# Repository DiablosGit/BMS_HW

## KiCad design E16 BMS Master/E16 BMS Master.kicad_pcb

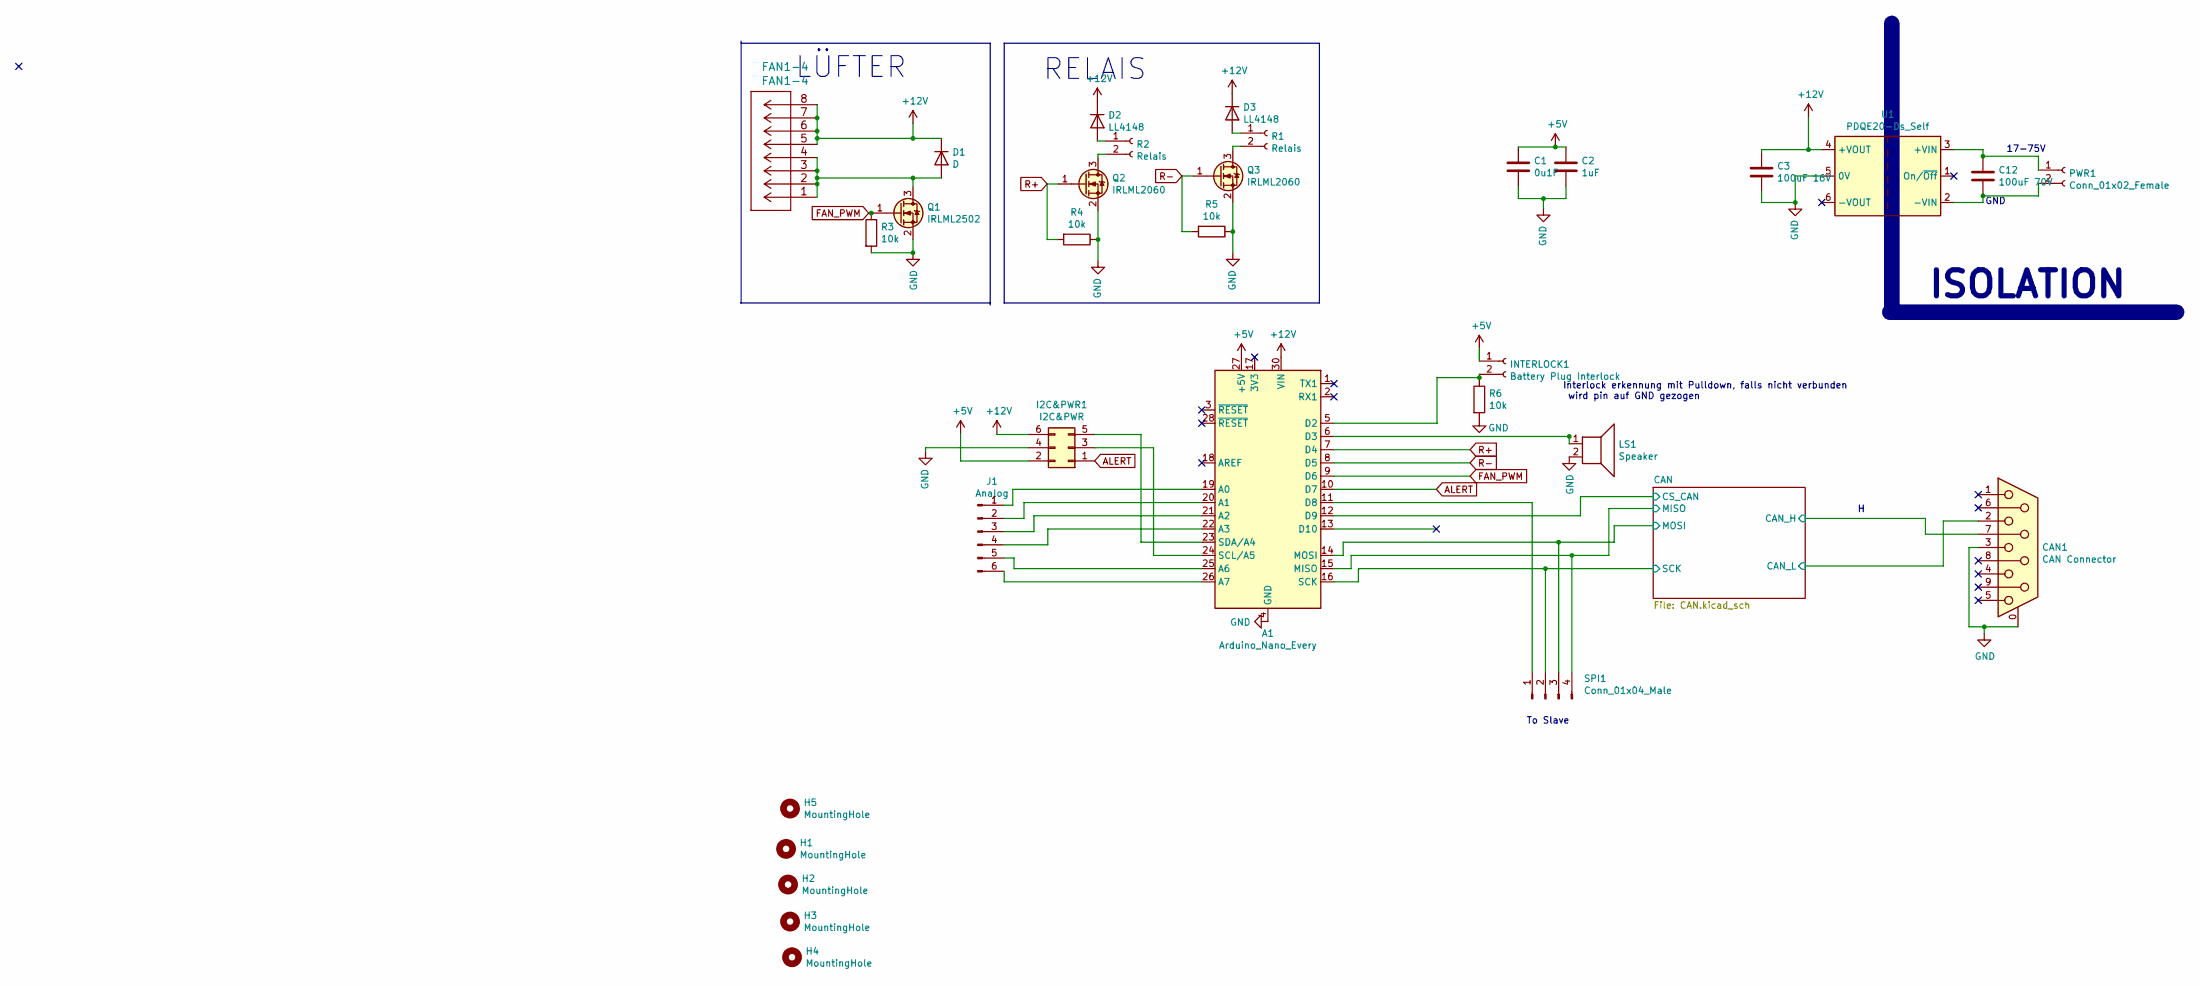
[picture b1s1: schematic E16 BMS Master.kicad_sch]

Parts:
A1: Arduino_Nano_Every; Arduino_Nano
C1: 0u1F; C_1206_3216Metric_Pad1.33x1.80mm_HandSolder
C2: 1uF; C_1206_3216Metric_Pad1.33x1.80mm_HandSolder
C3: 100uF 16V; C_1206_3216Metric_Pad1.33x1.80mm_HandSolder
C12: 100uF 70V; C_1206_3216Metric_Pad1.33x1.80mm_HandSolder
CAN1: CAN Connector; DSUB-9_Female_Horizontal_P2.77x2.84mm_EdgePinOffset7.70mm_H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
D1: D; D_MiniMELF
D2, D3: LL4148; D_MiniMELF
FAN1-4: FAN1-4; 449145803
H1, H2, H3, H4: MountingHole; MountingHole_3.2mm_M3_ISO7380
H5: MountingHole; FTAG3
I2C&PWR1: I2C&PWR; IDC-Header_2x03_P2.54mm_Horizontal
INTERLOCK1: Battery Plug Interlock; 430450228
J1: Analog; JST_XH_B6B-XH-AM_1x06_P2.50mm_Vertical
LS1: Speaker; Buzzer4mmPIN
PWR1: Conn_01x02_Female; 430450228
Q1: IRLML2502; SOT-23_Handsoldering
Q2, Q3: IRLML2060; SOT-23_Handsoldering
R1, R2: Relais; 430450228
R3, R4, R5, R6: 10k; R_1206_3216Metric_Pad1.30x1.75mm_HandSolder
SPI1: Conn_01x04_Male; JST_XH_S4B-XH-A_1x04_P2.50mm_Horizontal
U1: PDQE20-Ds_Self; Converter_DCDC_XP_POWER_JTDxxxxxxx_THT_self

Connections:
+5V: A1.27 (+5V), C1.1, C2.1, I2C&PWR1.2, INTERLOCK1.1; also elsewhere on the board
+12V: A1.30 (VIN), C3.1, D1.1 (K), D2.1 (K), D3.1 (K), FAN1-4.5, FAN1-4.6, FAN1-4.7, FAN1-4.8, I2C&PWR1.6, U1.4 (+VOUT)
/CAN/CAN_H: CAN1.7; also elsewhere on the board
/CAN/CAN_L: CAN1.2; also elsewhere on the board
/CAN/CS_CAN: A1.12 (D9); also elsewhere on the board
/CAN/MISO: A1.15 (MISO), SPI1.4; also elsewhere on the board
/CAN/MOSI: A1.14 (MOSI), SPI1.3; also elsewhere on the board
/CAN/SCK: A1.16 (SCK), SPI1.2; also elsewhere on the board
ALERT: A1.10 (D7), I2C&PWR1.1
FAN_PWM: A1.9 (D6), Q1.1 (G), R3.1
GND: A1.4 (GND), A1.29 (GND), C1.2, C2.2, C3.2, CAN1.0 (PAD), CAN1.3, I2C&PWR1.4, LS1.2, Q1.2 (S), Q2.2 (S), Q3.2 (S), R3.2, R4.1, R5.1, R6.2, U1.5 (0V); also elsewhere on the board
unnamed: A1.19 (A0), J1.1
unnamed: A1.20 (A1), J1.2
unnamed: A1.21 (A2), J1.3
unnamed: A1.22 (A3), J1.4
unnamed: A1.25 (A6), J1.5
unnamed: A1.26 (A7), J1.6
unnamed: A1.5 (D2), INTERLOCK1.2, R6.1
unnamed: A1.6 (D3), LS1.1
unnamed: A1.11 (D8), SPI1.1
unnamed: A1.24 (SCL/A5), I2C&PWR1.3
unnamed: A1.23 (SDA/A4), I2C&PWR1.5
unnamed: D1.2 (A), FAN1-4.1, FAN1-4.2, FAN1-4.3, FAN1-4.4, Q1.3 (D)
unnamed: D2.2 (A), R2.1
unnamed: D3.2 (A), R1.1
unnamed: C12.1, PWR1.1, U1.3 (+VIN)
unnamed: C12.2, PWR1.2, U1.2 (-VIN)
unnamed: Q2.3 (D), R2.2
unnamed: Q3.3 (D), R1.2
R+: A1.7 (D4), Q2.1 (G), R4.2
R-: A1.8 (D5), Q3.1 (G), R5.2

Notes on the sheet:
GND
ISOLATION
Interlock erkennung mit Pulldown, falls nicht verbunden wird pin auf GND gezogen
17-75V
RELAIS
LÜFTER
To Slave

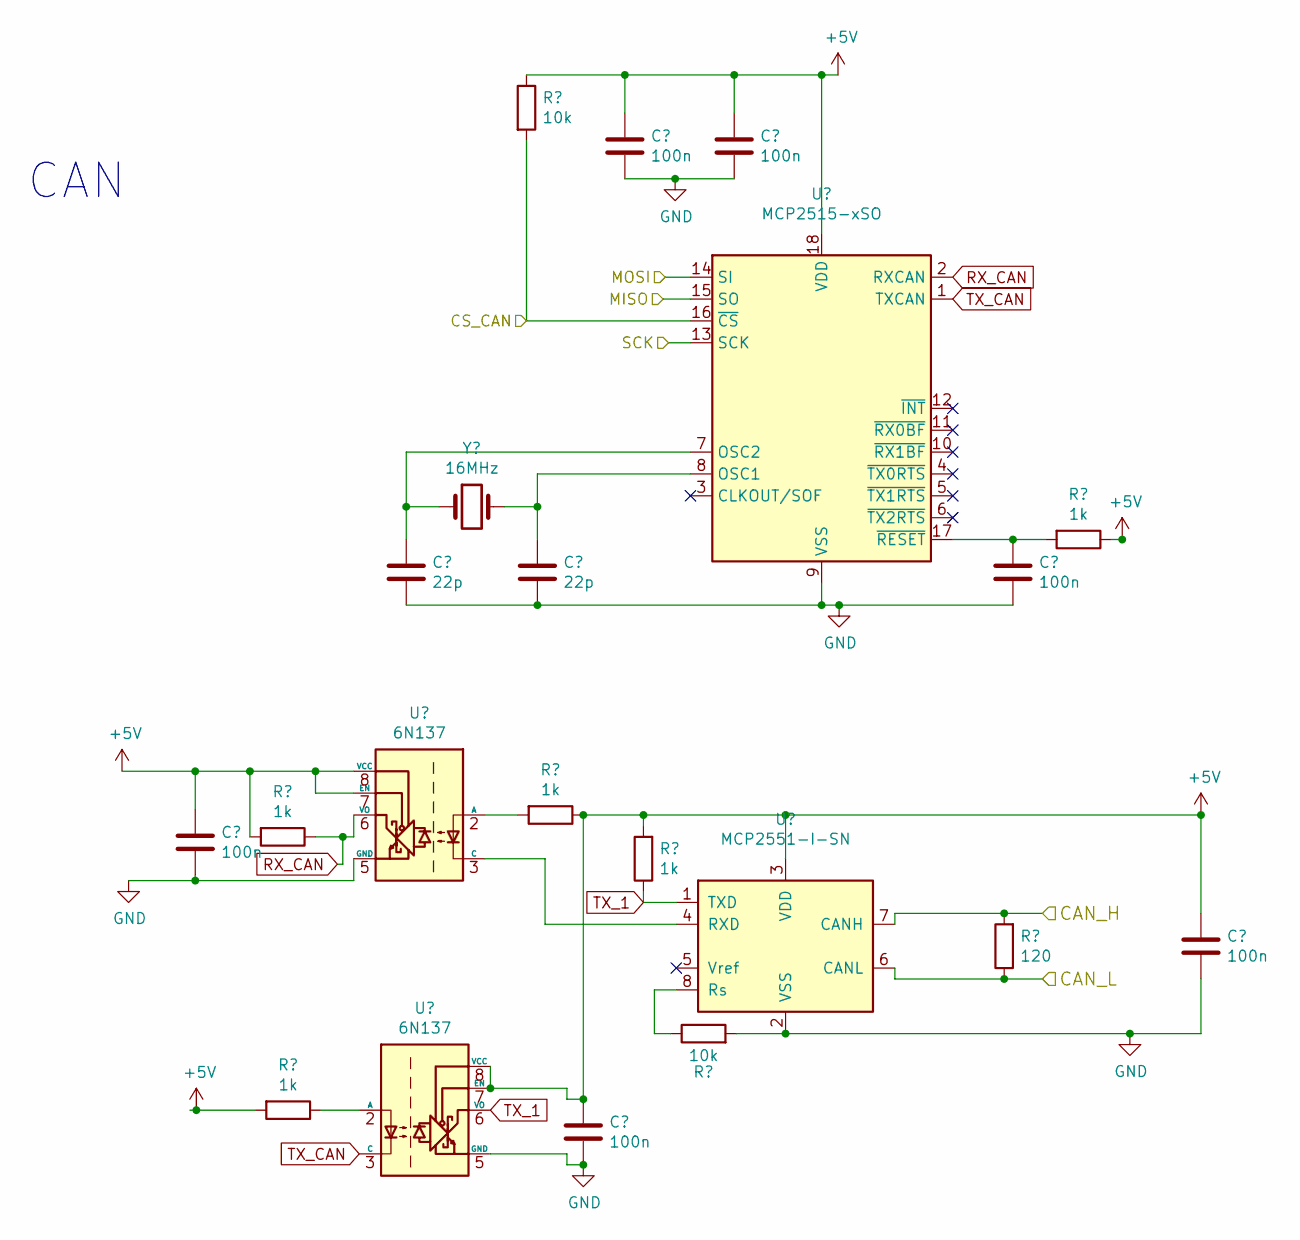
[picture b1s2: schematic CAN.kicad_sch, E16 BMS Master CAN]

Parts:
C4, C7, C8, C9, C10, C11: 100n; C_1206_3216Metric_Pad1.33x1.80mm_HandSolder
C5, C6: 22p; C_1206_3216Metric_Pad1.33x1.80mm_HandSolder
R7, R8, R10, R11, R14: 1k; R_1206_3216Metric_Pad1.30x1.75mm_HandSolder
R9, R12: 10k; R_1206_3216Metric_Pad1.30x1.75mm_HandSolder
R13: 120; R_1206_3216Metric_Pad1.30x1.75mm_HandSolder
U2, U3: 6N137; DIP-8_W7.62mm
U4: MCP2551-I-SN; SOIC-8_3.9x4.9mm_P1.27mm
U5: MCP2515-xSO; SOIC-18W_7.5x11.6mm_P1.27mm
Y1: 16MHz; Crystal_SMD_HC49-SD_HandSoldering

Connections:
+5V: C4.1, C7.1, C8.1, C9.1, C11.1, R7.2, R8.2, R9.1, R10.1, R11.2, R14.1, U2.7 (EN), U2.8 (VCC), U3.7 (EN), U3.8 (VCC), U4.3 (VDD), U5.18 (VDD); also elsewhere on the board
/CAN/CAN_H: R13.2, U4.7 (CANH); also elsewhere on the board
/CAN/CAN_L: R13.1, U4.6 (CANL); also elsewhere on the board
/CAN/CS_CAN: R9.2, U5.16 (~CS); also elsewhere on the board
/CAN/MISO: U5.15 (SO); also elsewhere on the board
/CAN/MOSI: U5.14 (SI); also elsewhere on the board
/CAN/SCK: U5.13 (SCK); also elsewhere on the board
GND: C4.2, C5.2, C6.2, C7.2, C8.2, C9.2, C10.2, C11.2, R12.2, U2.5 (GND), U3.5 (GND), U4.2 (VSS), U5.9 (VSS); also elsewhere on the board
unnamed: R10.2, U2.2 (A)
unnamed: U2.3 (C), U4.4 (RXD)
unnamed: R8.1, U3.2 (A)
unnamed: R12.1, U4.8 (Rs)
unnamed: C6.1, U5.8 (OSC1), Y1.2
unnamed: C5.1, U5.7 (OSC2), Y1.1
unnamed: C10.1, R14.2, U5.17 (~RESET)
RX_CAN: R7.1, U2.6 (VO), U5.2 (RXCAN)
TX_1: R11.1, U3.6 (VO), U4.1 (TXD)
TX_CAN: U3.3 (C), U5.1 (TXCAN)

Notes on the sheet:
CAN

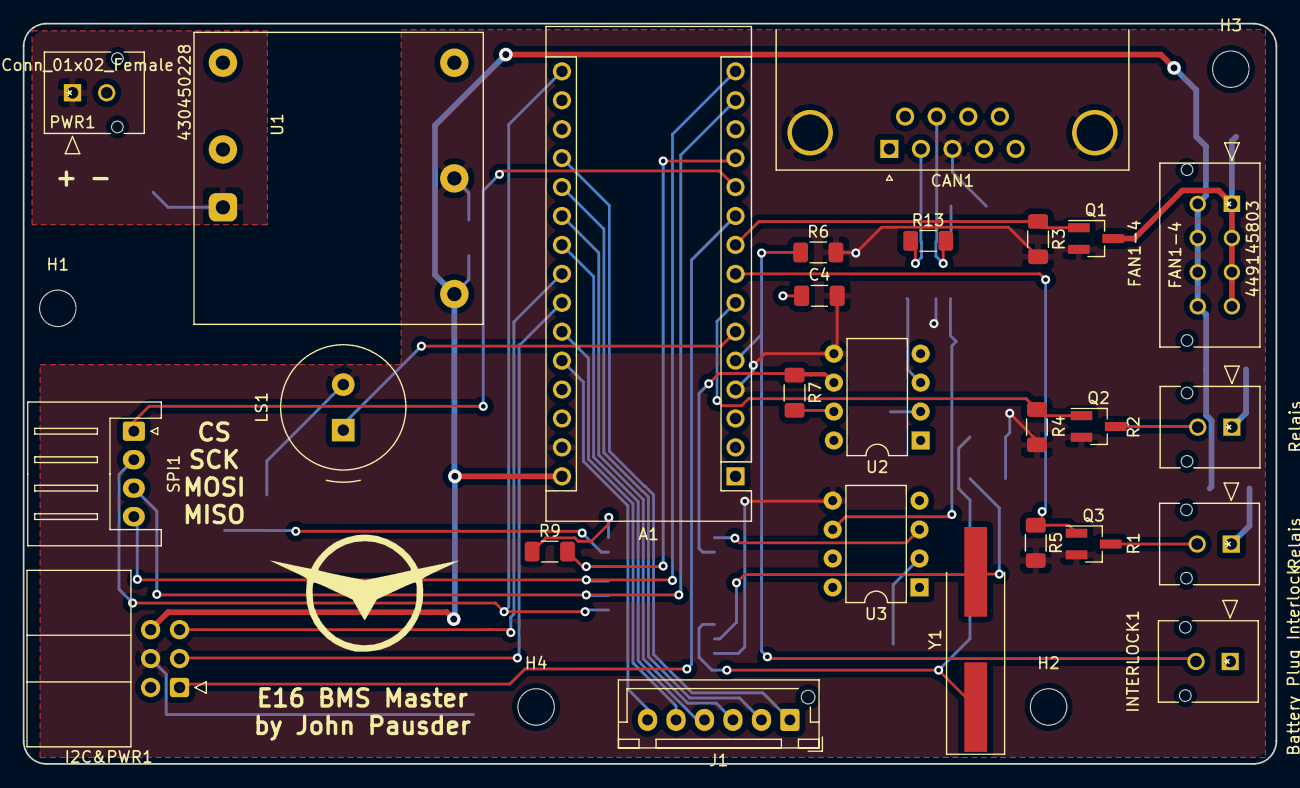
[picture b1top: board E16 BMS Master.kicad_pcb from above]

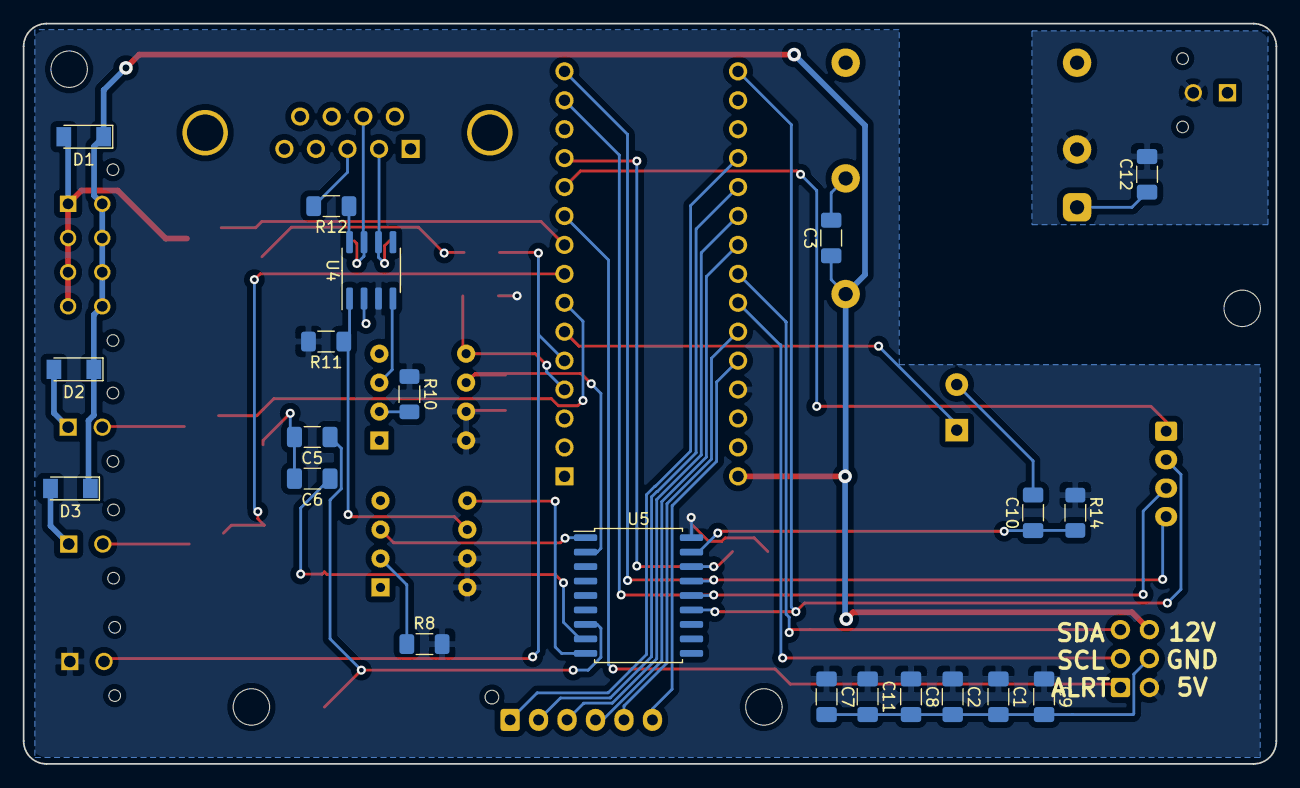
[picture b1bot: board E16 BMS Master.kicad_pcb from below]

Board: 2 copper layers, 110.0 x 65.0 mm, 52 parts (21 on the bottom side), 41 nets.

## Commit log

2025-03-27 added HW Files
2025-03-27 aufräumen
2025-03-31 added 5k pullup for MISO

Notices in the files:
parts and their libraries:
Copyright 2021 Accelerated Designs. All rights reserved.
